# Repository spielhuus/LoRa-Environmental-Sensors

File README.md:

# LoRa Environmental Sensors 

</img>

Arduino based board for a Atmospheric Sensor BME280 LoRaWan Node. The LoRa Node measures barometric pressure, humidity, and temperature every 5 min. After the measurements, the ATtiny85 goes into sleep mode and is awakened by the watchdog timer. The RFM module sends the values to the TTN backend with Activation by Personalization (ABP) a fixed spreading factor and one of the four random channels. This project is based on the TinyLoRa-BME280 project [1].

## BOM

|Ref|Value|Description|
| --- | --- | --- | 
|BT1| [3034](https://spielhuus.github.io/LoRa-Environmental-Sensors/3034.pdf) |Battery Cell Holder|3034 1x20mm](https://www.keyelco.com/product.cfm/product_id/798)| 
|BT1| CR2032 |Battery Cell CR2032 (210 – 230 mAh)| 
|U1| [BME280](https://spielhuus.github.io/LoRa-Environmental-Sensors/BST-BME280_DS001-10.pdf) | [SparkFun BME280](https://github.com/sparkfun/SparkFun_BME280_Breakout_Board)|
|U2| [ATtiny85-20SU](https://spielhuus.github.io/LoRa-Environmental-Sensors/atmel-2586-avr-8-bit-microcontroller-attiny25-attiny45-attiny85_datasheet.pdf) | Atmel 8-bit AVR Microcontroller|
|U3| [RFM95W-868S2](https://spielhuus.github.io/LoRa-Environmental-Sensors/RFM95_96_97_98W.pdf) | Low Power Long Range Transceiver Module |
| - | Wire | Wire for the antenna, 8.6 cm |

The ATmega microprocessor needs an arduino bootloader. To burn a bootloader to the blank chip see [2]

## Wiring

| ATtiny85 | RFM95 | BME280 |
| -------- | ----- | ------ |
| PB3 | | CS (Slave Select) |
| PB4 | NSS (Slave Select) | |
| PB2 | SCK | SCK |
| PB1(DO) | MOSI | SDI |
| PB0(DI) | MISO | SDO |

## Installation

The Arduino IDE has to be properly installed. 

Add the Libraries to you IDE:

- Install the Attiny Baord Manager
  - Under Preferences > Additional Boards Manager URLs: https://raw.githubusercontent.com/damellis/attiny/ide-1.6.x-boards-manager/package_damellis_attiny_index.json

  Multiple managers can be separated with a comma.

- Install TinyLoRa-BME280 v1.1
  - Download the ZIP archive from [TinyLoRa-BME280 v1.1](https://github.com/ClemensRiederer/TinyLoRa-BME280_v1.1)
  - Install the ZIP archive in the Arduino Library Manager

- Open Examples > TinyLoRa-BME280_v1.1-master > ATtiny_LoRa_BME280
  - Edit NwkSkey, AppSkey, DevAddr
  - Change the Spreading Factor in ATtinyLoRa.cpp
  - The Sleep time can be set with the SLEEP_TOTAL var.

- Burn the sketch to the Chip using an Arduino UNO [2]
  - Burn a bootloader first to set the fuses correctly

## Payload Format

The Payload is encoded as byte array.

| byte | content |
| ---- | ------- |
| 0..1 | temperature (*100) |
| 2..3 | humidity (*100) |
| 4..8 | barometric pressure |

To decode the values add this code in the TTM Console as decoder under Paload Formats.

```
function Decoder(bytes, port) {
  temp = ((bytes[0]) << 8)
              + ((bytes[1]));
  hum = ((bytes[2]) << 8)
              + ((bytes[3]));
  pres = ((bytes[4]) << 24)
              + ((bytes[5]) << 16)
              + ((bytes[6]) << 8)
              + ((bytes[7]));

  return {
    pressure: ( pres / 100 ),
    temperature: ( temp / 100 ),
    humidity: ( hum / 100 )
  };
}
```

## Links

1. [TinyLoRa-BME280 v1.1](https://github.com/ClemensRiederer/TinyLoRa-BME280_v1.1)
2. [Programming ATtiny85 with Arduino Uno](https://www.hackster.io/arjun/programming-attiny85-with-arduino-uno-afb829)

## License

[License CC BY 4.0](http://creativecommons.org/licenses/by/4.0/) - Attribution 4.0 International

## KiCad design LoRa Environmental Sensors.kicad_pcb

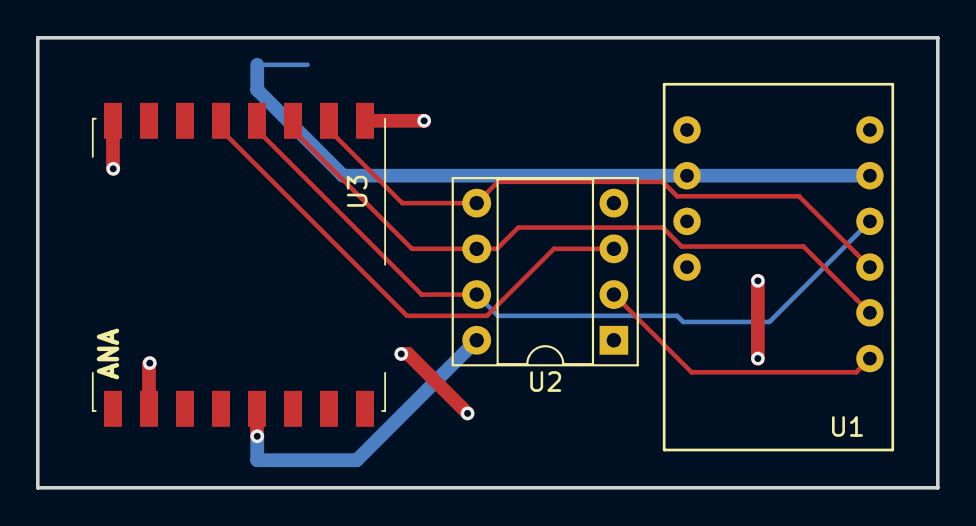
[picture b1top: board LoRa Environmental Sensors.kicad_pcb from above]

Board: 2 copper layers, 50.0 x 25.0 mm, 4 parts (1 on the bottom side), 7 nets.

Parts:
BT1: Battery_Cell; BatteryHolder_Keystone_3034_1x20mm
U1: BME280BreakoutBoard; Sparkfun bme280
U2: ATtiny85-20SU; DIP-8_W7.62mm_Socket
U3: RFM95W-868S2; HOPERF_RFM9XW_SMD

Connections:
/CS: U1.10, U2.2
/MISO: U1.8, U2.5, U3.2
/MOSI: U1.9, U2.6, U3.3
/NSS: U2.3, U3.5
/SCK: U1.7, U2.7, U3.4
GND: BT1.2, U1.1, U1.5, U2.4, U3.1, U3.8, U3.10
VCC: BT1.1, U1.2, U1.6, U2.8, U3.13

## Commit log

2018-11-25 update datasheets
2018-11-25 add gerber files
2018-11-25 update pcb
2018-11-25 update gerbers
2018-11-25 update gerber files
2018-12-17 add enclosure
2018-12-18 update enclosure
2018-12-23 update 3d model
2018-12-24 add new enclosure
2018-12-24 update sensor 02
2018-12-25 add outdoor enclosure
2018-12-25 sensor 4
2018-12-26 update final prodcut picture
